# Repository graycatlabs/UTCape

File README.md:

# UTCape

A BeagleBone Black cape to support unit tests in software libraries like PyBBIO 
and Bonsescript. 

The current concept would allow testing of GPIO, UART, SPI, I2C, ADC, eCAP, PWM,
and eQEP software.

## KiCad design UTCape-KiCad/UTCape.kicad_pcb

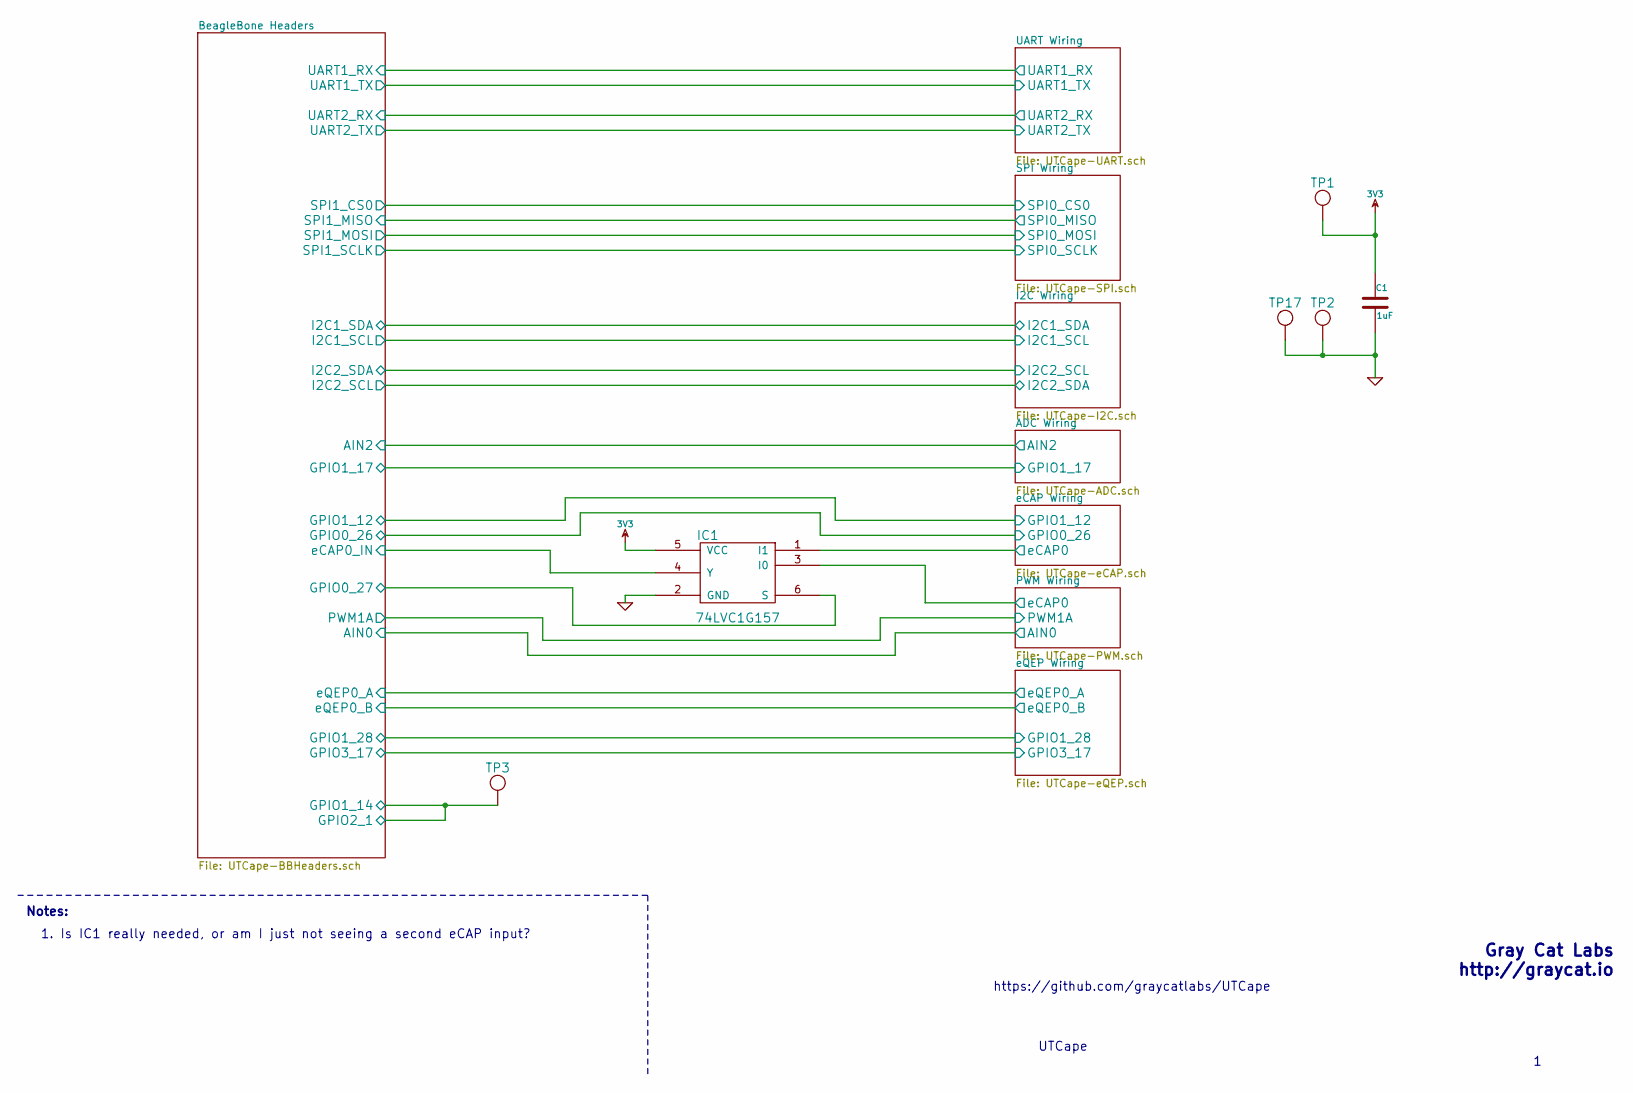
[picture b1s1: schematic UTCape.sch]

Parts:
C1: 1uF
IC1: 74LVC1G157
TP1, TP2, TP3, TP17: TEST_POINT

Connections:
3V3: C1.1, IC1.5 (VCC), TP1.1; also elsewhere on the board
/BeagleBone Headers/GPIO0_27: IC1.6 (S); also elsewhere on the board
/BeagleBone Headers/GPIO2_1: TP3.1; also elsewhere on the board
/BeagleBone Headers/PWM1A: IC1.3 (I0); also elsewhere on the board
/BeagleBone Headers/eCAP0_IN: IC1.4 (Y); also elsewhere on the board
/eCAP Wiring/eCAP0: IC1.1 (I1); also elsewhere on the board
GND: C1.2, IC1.2 (GND), TP2.1, TP17.1; also elsewhere on the board

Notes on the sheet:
UTCape
Gray Cat Labs http://graycat.io
https://github.com/graycatlabs/UTCape
Notes:
1. Is IC1 really needed, or am I just not seeing a second eCAP input?

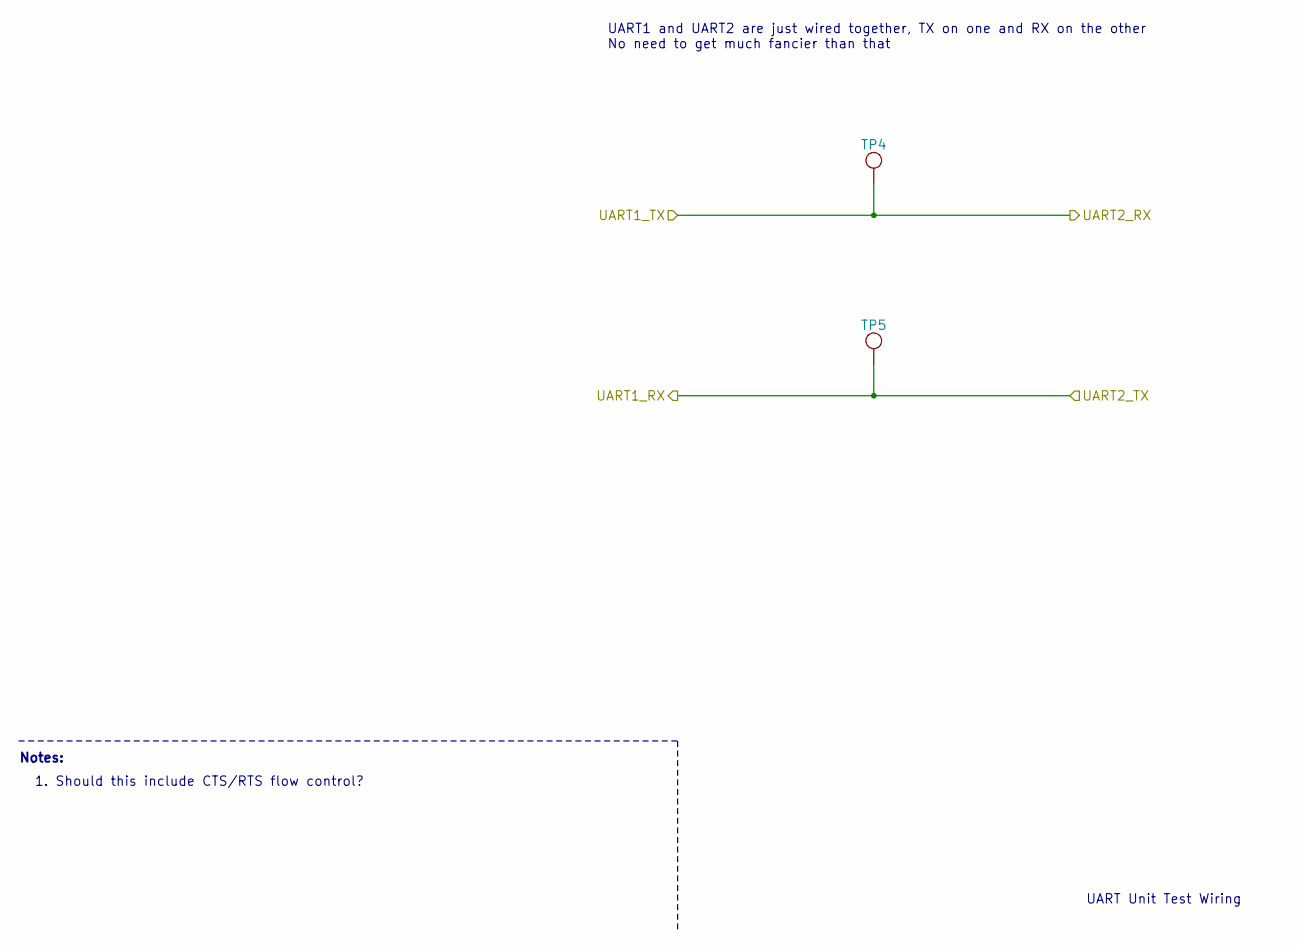
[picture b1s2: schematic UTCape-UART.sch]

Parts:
TP4, TP5: TEST_POINT

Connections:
/BeagleBone Headers/UART1_RX: TP5.1; also elsewhere on the board
/BeagleBone Headers/UART1_TX: TP4.1; also elsewhere on the board

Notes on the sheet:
UART Unit Test Wiring
UART1 and UART2 are just wired together, TX on one and RX on the other No need to get much fancier than that
1. Should this include CTS/RTS flow control?
Notes:

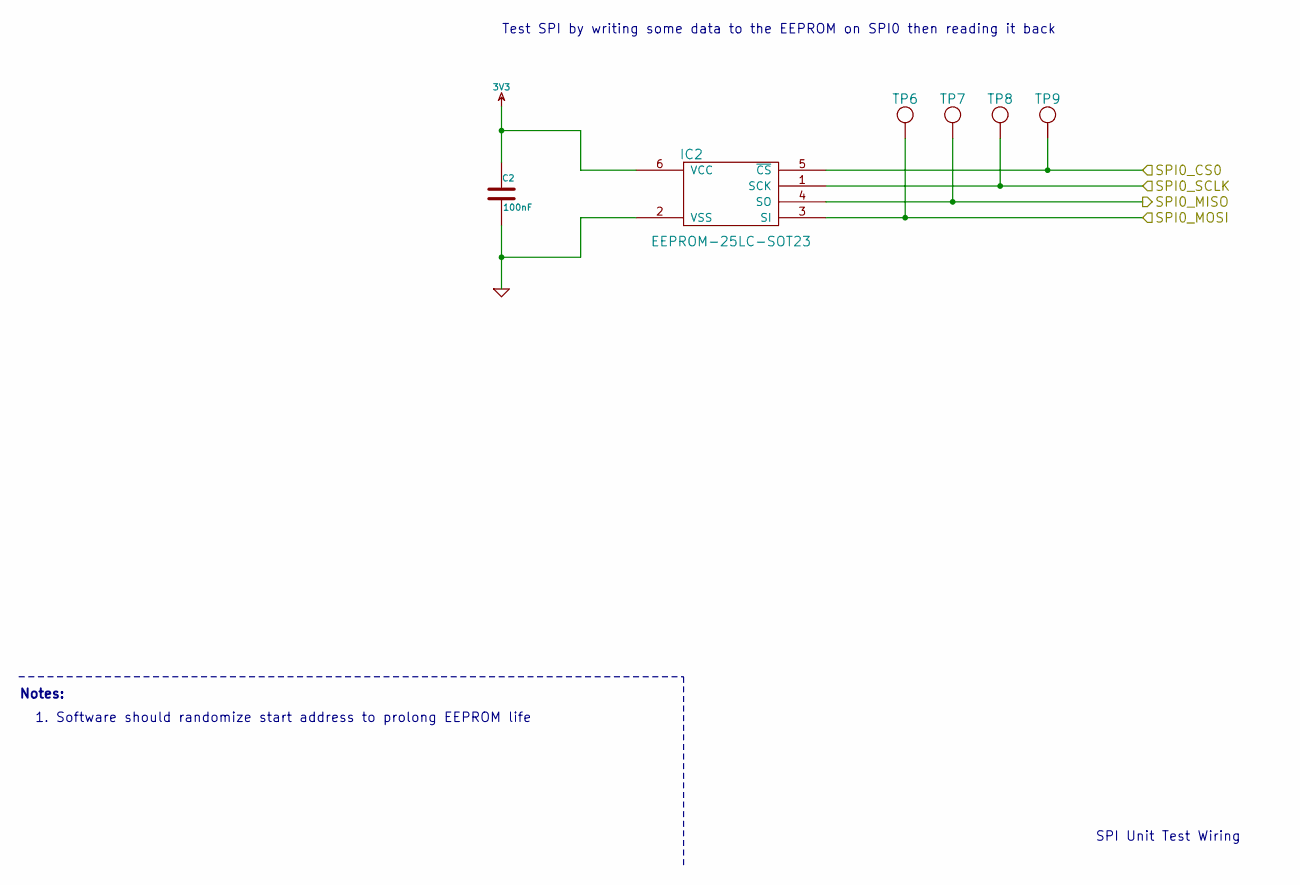
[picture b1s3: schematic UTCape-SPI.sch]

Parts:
C2: 100nF
IC2: EEPROM-25LC-SOT23
TP6, TP7, TP8, TP9: TEST_POINT

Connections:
3V3: C2.1, IC2.6 (VCC); also elsewhere on the board
/SPI Wiring/SPI0_CS0: IC2.5 (~CS), TP9.1; also elsewhere on the board
/SPI Wiring/SPI0_MISO: IC2.4 (SO), TP7.1; also elsewhere on the board
/SPI Wiring/SPI0_MOSI: IC2.3 (SI), TP6.1; also elsewhere on the board
/SPI Wiring/SPI0_SCLK: IC2.1 (SCK), TP8.1; also elsewhere on the board
GND: C2.2, IC2.2 (VSS); also elsewhere on the board

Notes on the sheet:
SPI Unit Test Wiring
Test SPI by writing some data to the EEPROM on SPI0 then reading it back
Notes:
1. Software should randomize start address to prolong EEPROM life

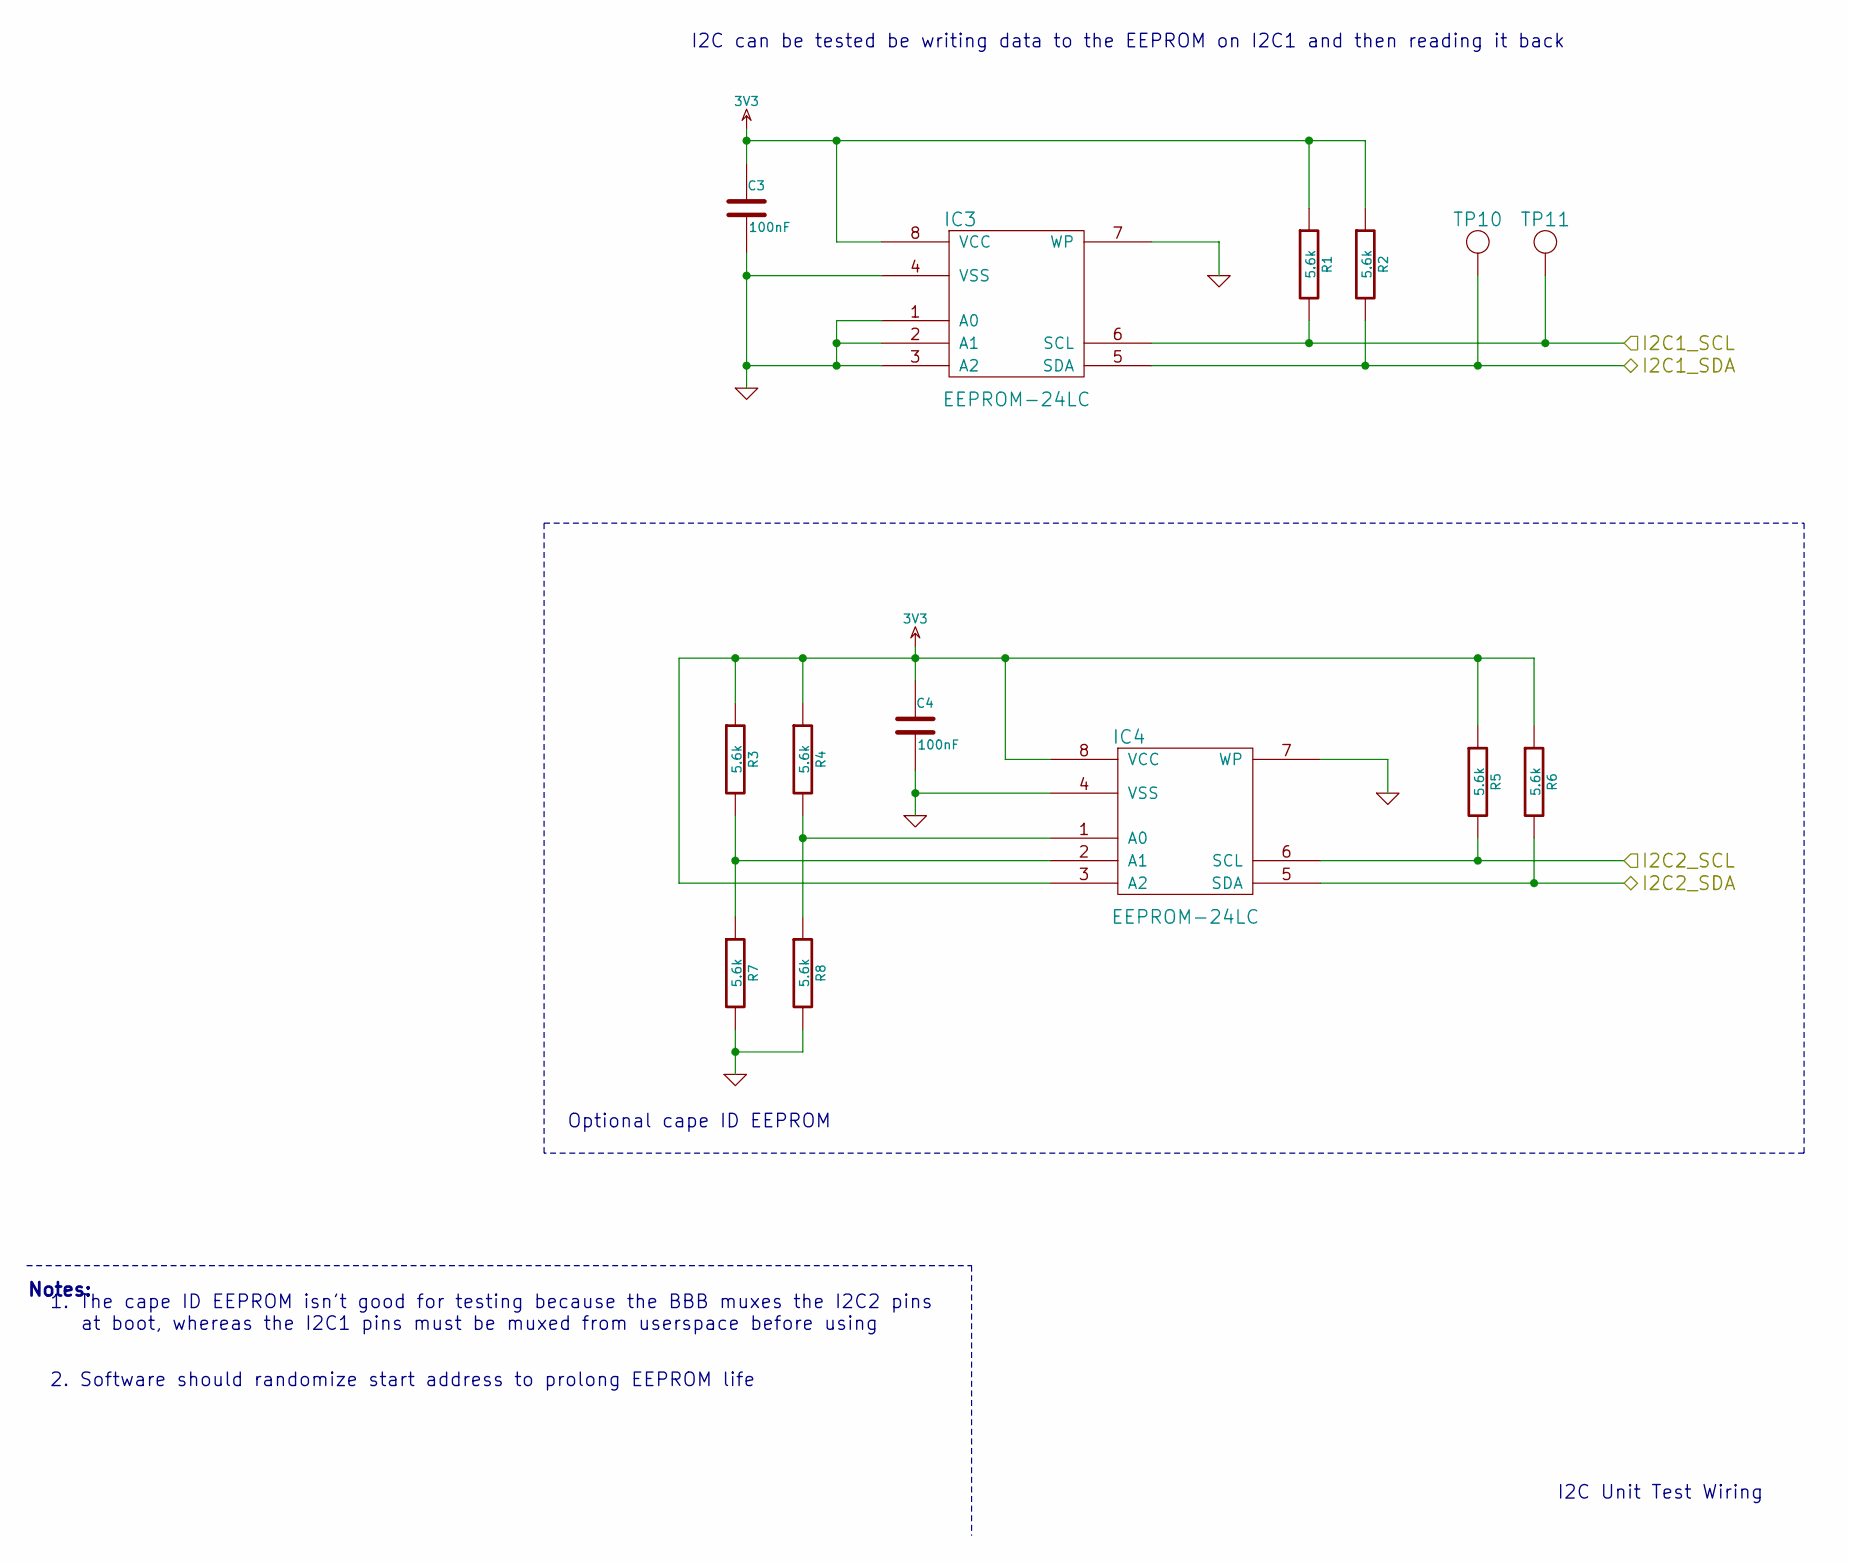
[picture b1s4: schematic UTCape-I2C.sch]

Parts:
C3, C4: 100nF
IC3, IC4: EEPROM-24LC
R1, R2, R3, R4, R5, R6, R7, R8: 5.6k
TP10, TP11: TEST_POINT

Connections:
3V3: C3.1, C4.1, IC3.8 (VCC), IC4.3 (A2), IC4.8 (VCC), R1.1, R2.1, R3.1, R4.1, R5.1, R6.1; also elsewhere on the board
/BeagleBone Headers/I2C1_SCL: IC3.6 (SCL), R1.2, TP11.1; also elsewhere on the board
/BeagleBone Headers/I2C1_SDA: IC3.5 (SDA), R2.2, TP10.1; also elsewhere on the board
/BeagleBone Headers/I2C2_SCL: IC4.5 (SDA), R6.2; also elsewhere on the board
/I2C Wiring/I2C2_SCL: IC4.6 (SCL), R5.2; also elsewhere on the board
GND: C3.2, C4.2, IC3.1 (A0), IC3.2 (A1), IC3.3 (A2), IC3.4 (VSS), IC3.7 (WP), IC4.4 (VSS), IC4.7 (WP), R7.2, R8.2; also elsewhere on the board
unnamed: IC4.1 (A0), R4.2, R8.1
unnamed: IC4.2 (A1), R3.2, R7.1

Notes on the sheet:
I2C Unit Test Wiring
Optional cape ID EEPROM
I2C can be tested be writing data to the EEPROM on I2C1 and then reading it back
Notes:
1. The cape ID EEPROM isn't good for testing because the BBB muxes the I2C2 pins at boot, whereas the I2C1 pins must be muxed from userspace before using
2. Software should randomize start address to prolong EEPROM life

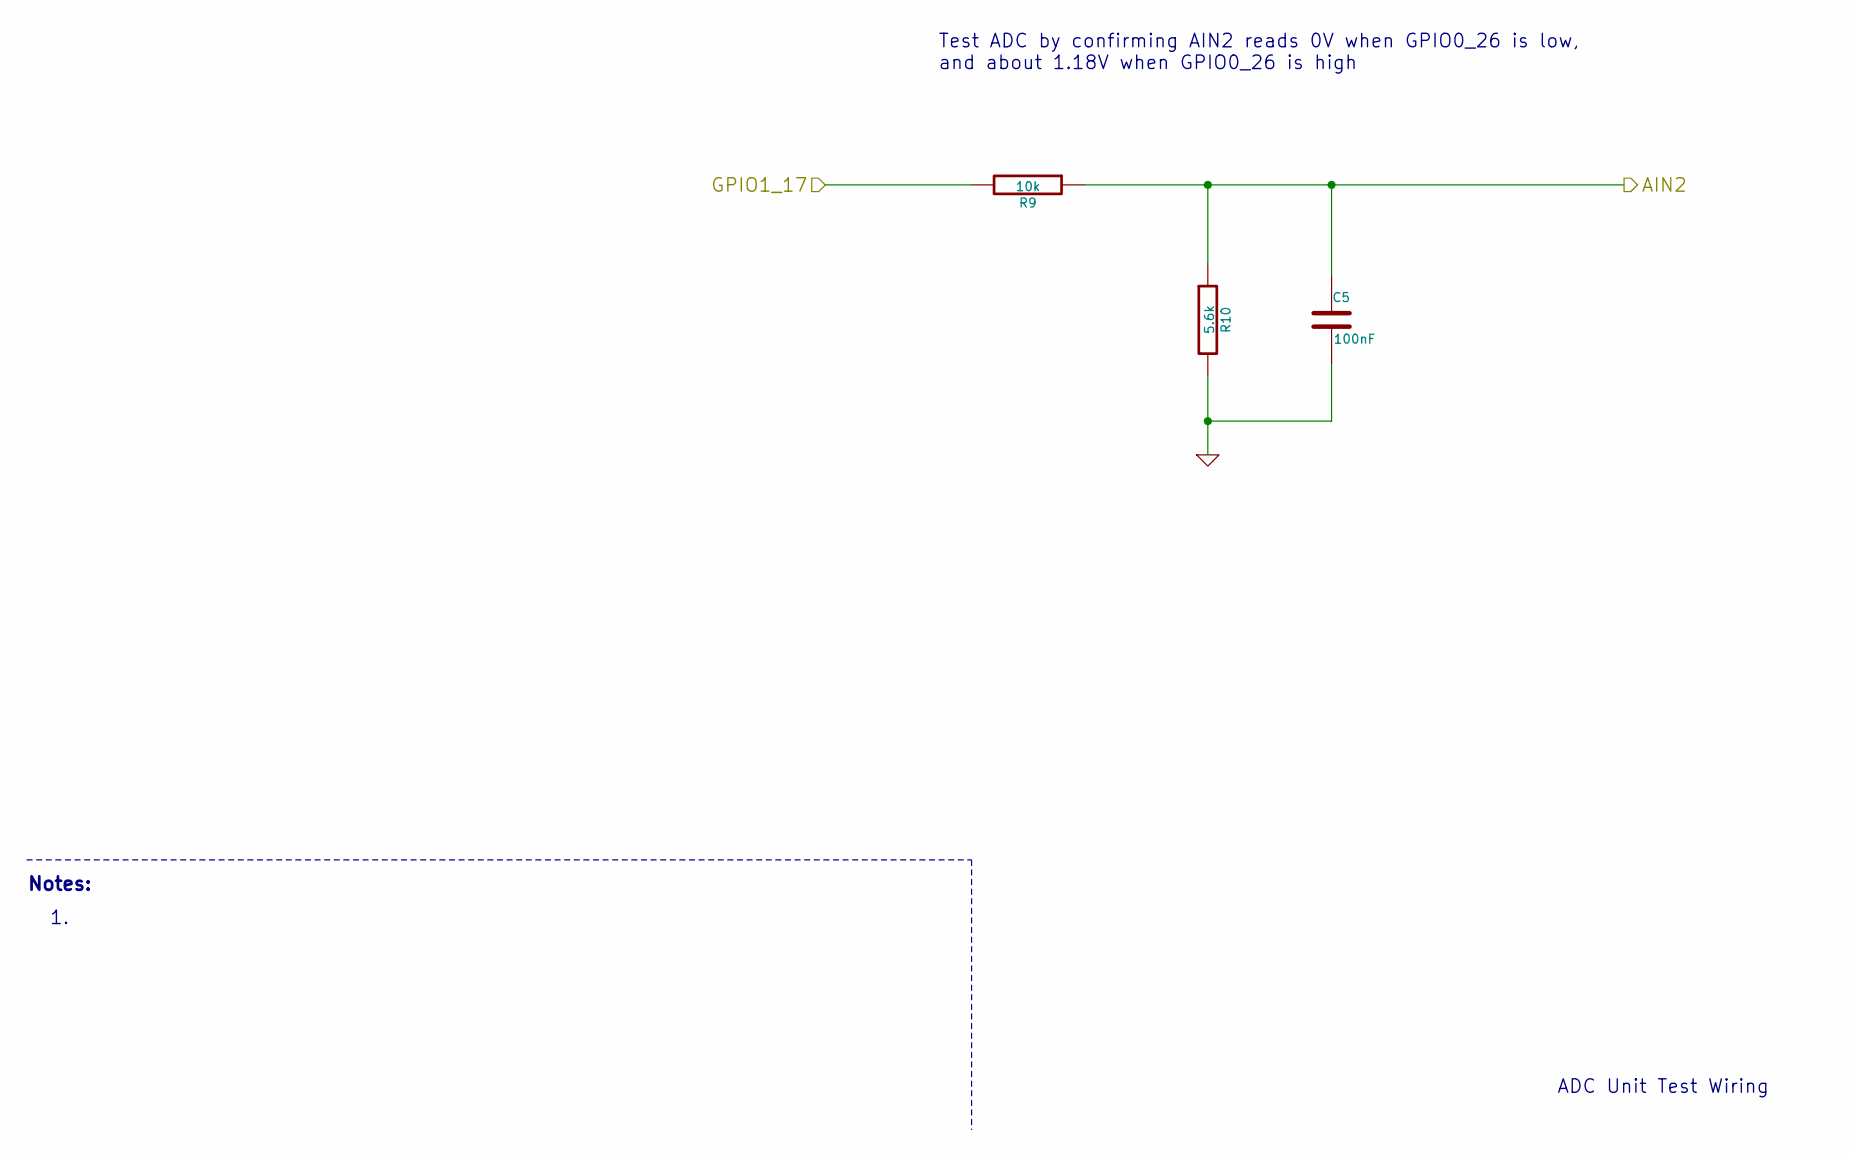
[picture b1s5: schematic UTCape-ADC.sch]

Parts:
C5: 100nF
R9: 10k
R10: 5.6k

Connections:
/ADC Wiring/AIN2: C5.1, R9.1, R10.1; also elsewhere on the board
/ADC Wiring/GPIO1_17: R9.2; also elsewhere on the board
GND: C5.2, R10.2; also elsewhere on the board

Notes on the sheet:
ADC Unit Test Wiring
Notes:
Test ADC by confirming AIN2 reads 0V when GPIO0_26 is low, and about 1.18V when GPIO0_26 is high

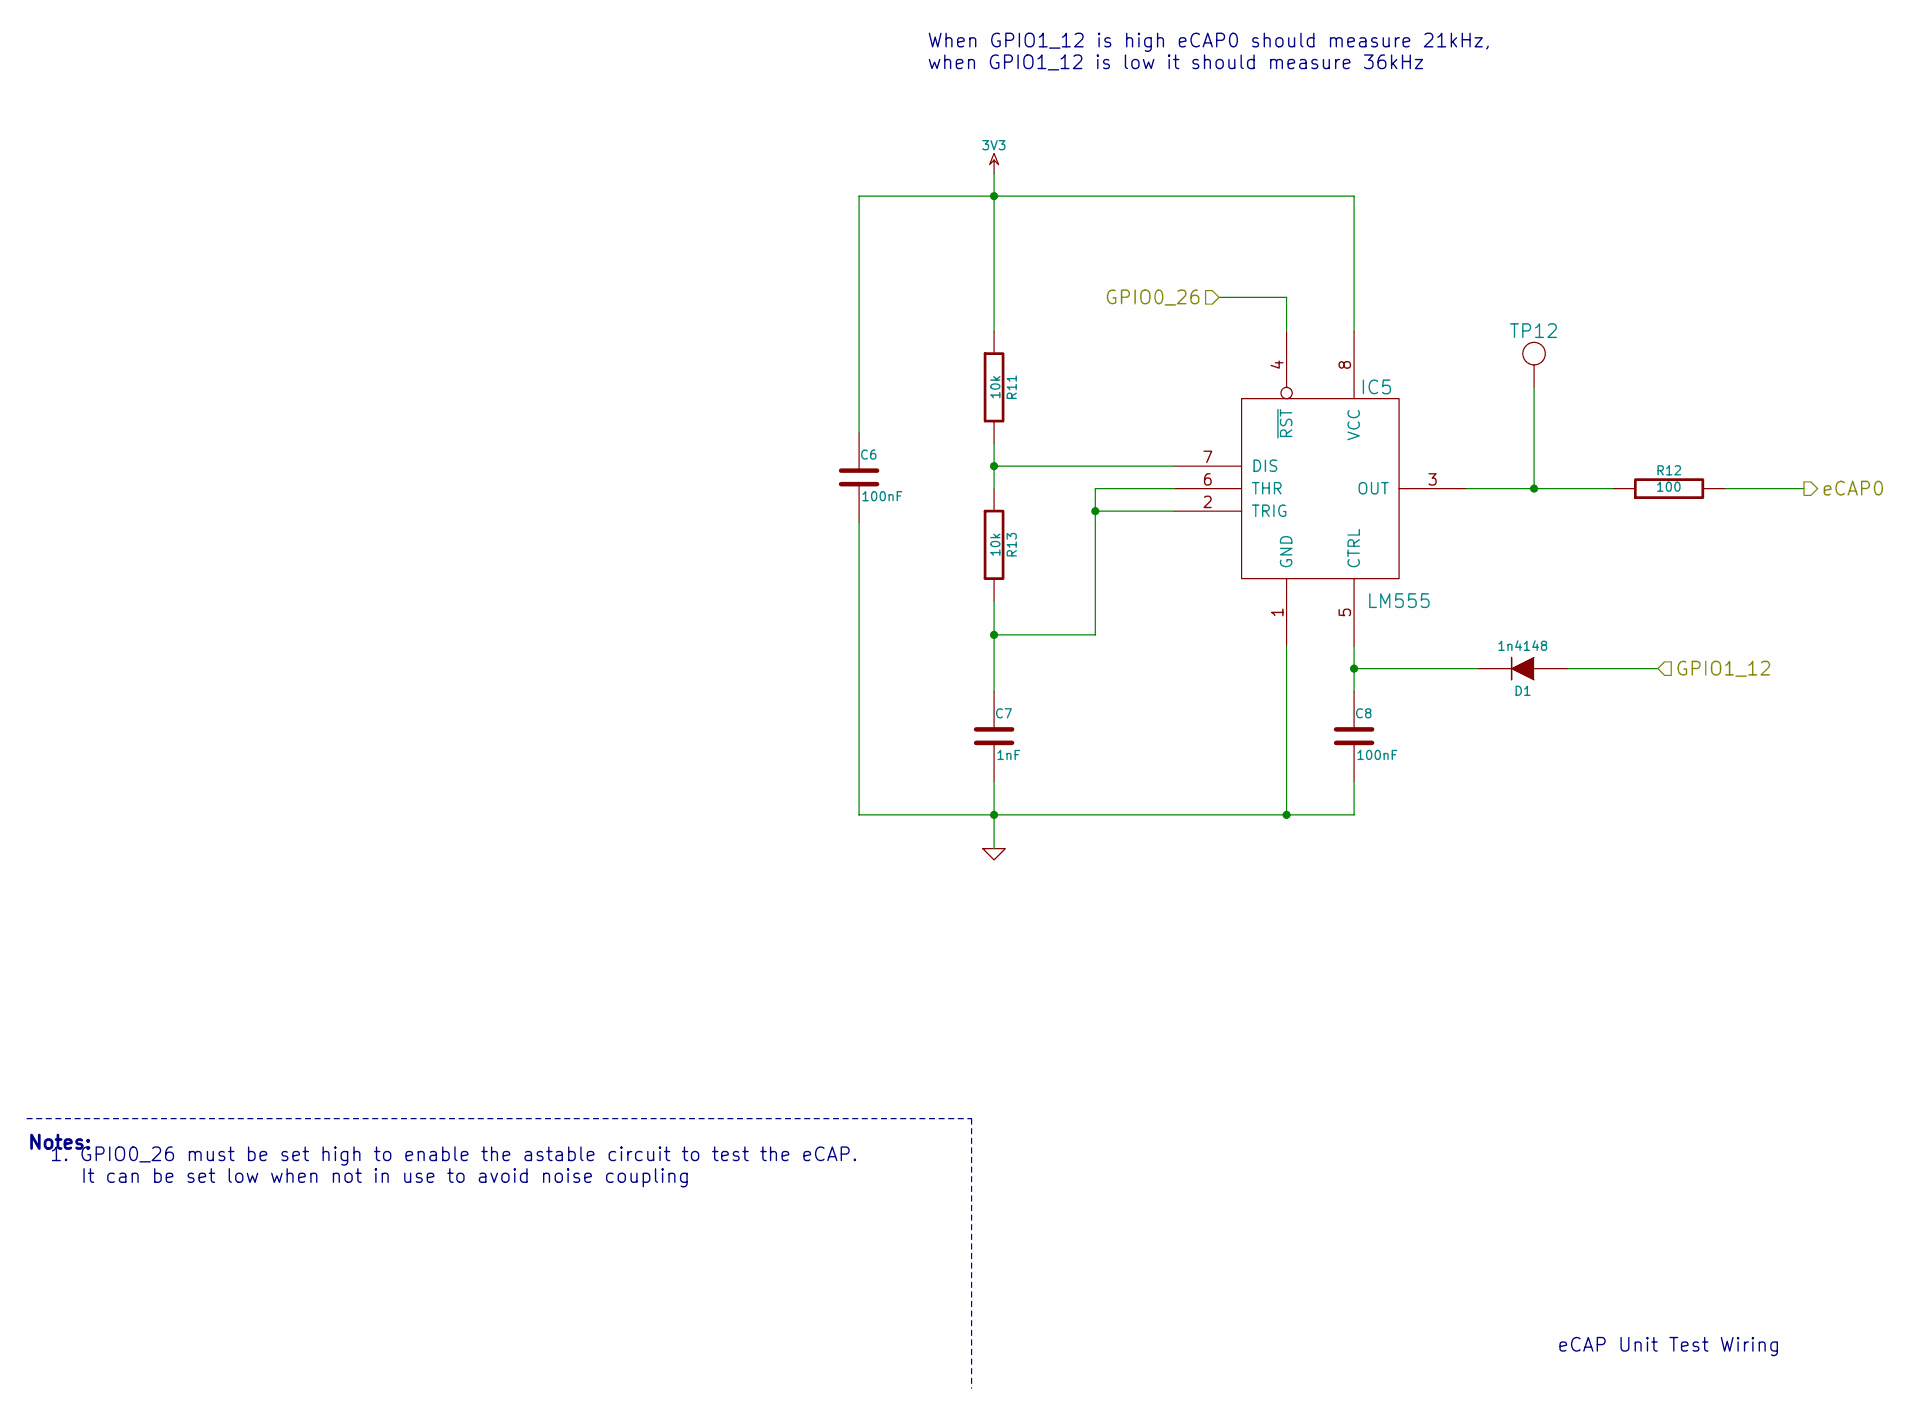
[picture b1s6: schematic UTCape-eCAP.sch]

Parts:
C6, C8: 100nF
C7: 1nF
D1: 1n4148
IC5: LM555
R11, R13: 10k
R12: 100
TP12: TEST_POINT

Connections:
3V3: C6.1, IC5.8 (VCC), R11.1; also elsewhere on the board
/BeagleBone Headers/GPIO0_26: IC5.4 (~RST); also elsewhere on the board
/BeagleBone Headers/GPIO1_12: D1.1 (A); also elsewhere on the board
/eCAP Wiring/eCAP0: R12.2; also elsewhere on the board
GND: C6.2, C7.2, C8.2, IC5.1 (GND); also elsewhere on the board
unnamed: IC5.7 (DIS), R11.2, R13.1
unnamed: IC5.3 (OUT), R12.1, TP12.1
unnamed: C8.1, D1.2 (K), IC5.5 (CTRL)
unnamed: C7.1, IC5.2 (TRIG), IC5.6 (THR), R13.2

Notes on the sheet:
Notes:
1. GPIO0_26 must be set high to enable the astable circuit to test the eCAP. It can be set low when not in use to avoid noise coupling
When GPIO1_12 is high eCAP0 should measure 21kHz, when GPIO1_12 is low it should measure 36kHz
eCAP Unit Test Wiring

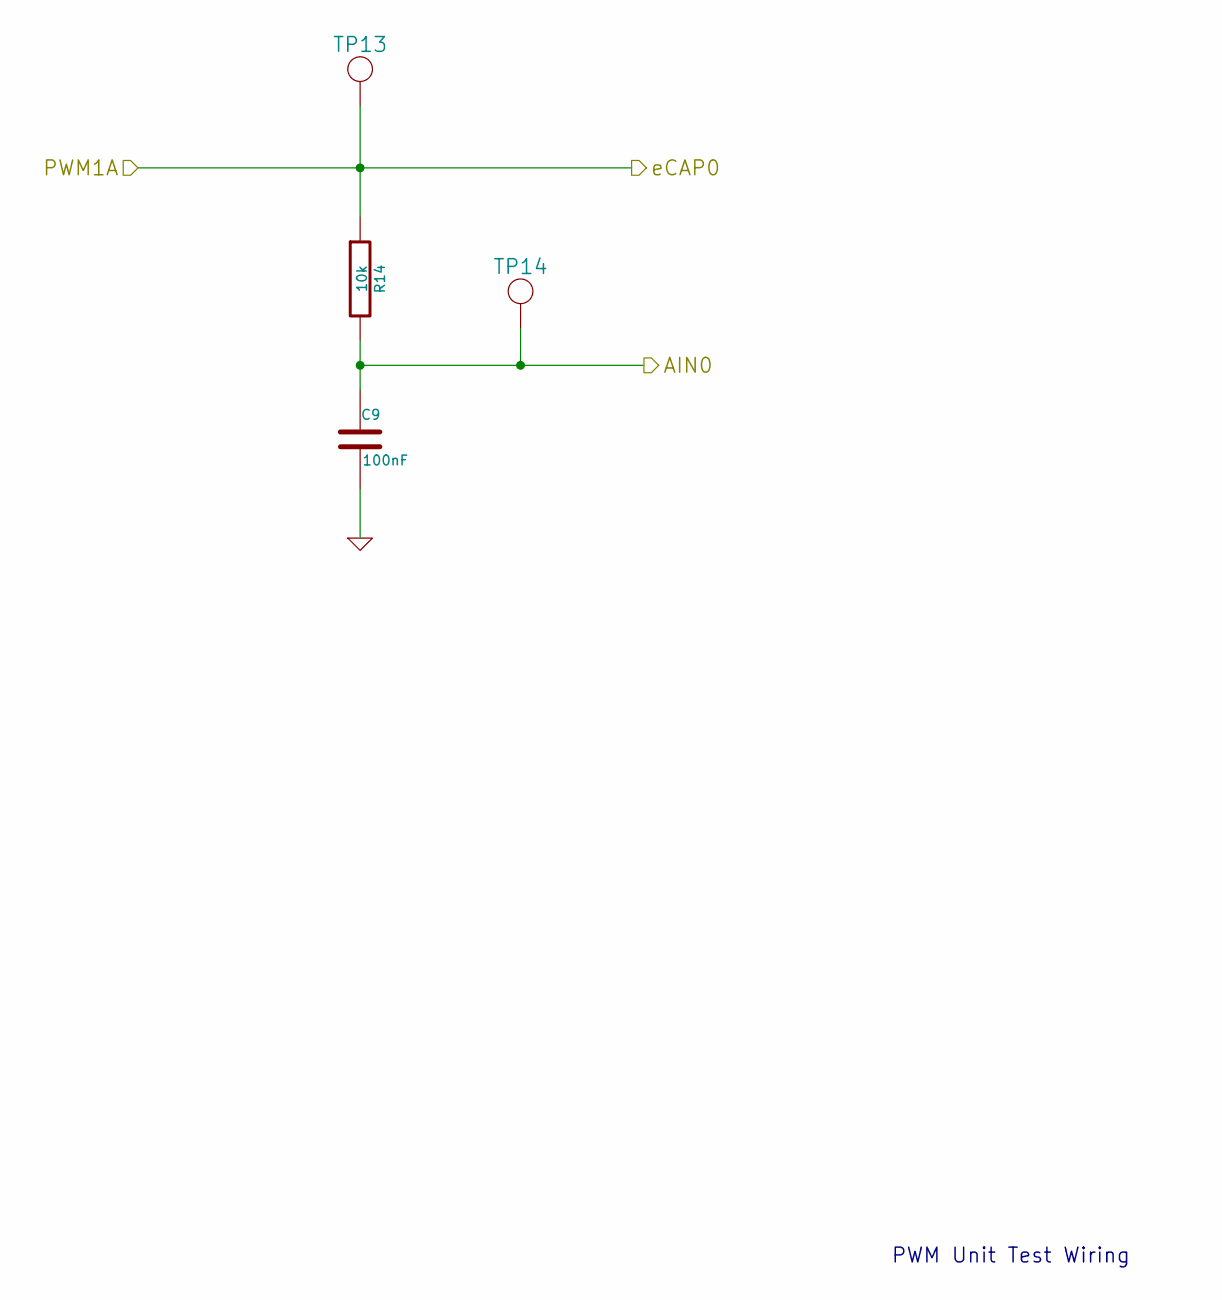
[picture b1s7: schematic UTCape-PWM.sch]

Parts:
C9: 100nF
R14: 10k
TP13, TP14: TEST_POINT

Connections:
/BeagleBone Headers/AIN0: C9.1, R14.2, TP14.1; also elsewhere on the board
/BeagleBone Headers/PWM1A: R14.1, TP13.1; also elsewhere on the board
GND: C9.2; also elsewhere on the board

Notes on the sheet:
PWM Unit Test Wiring

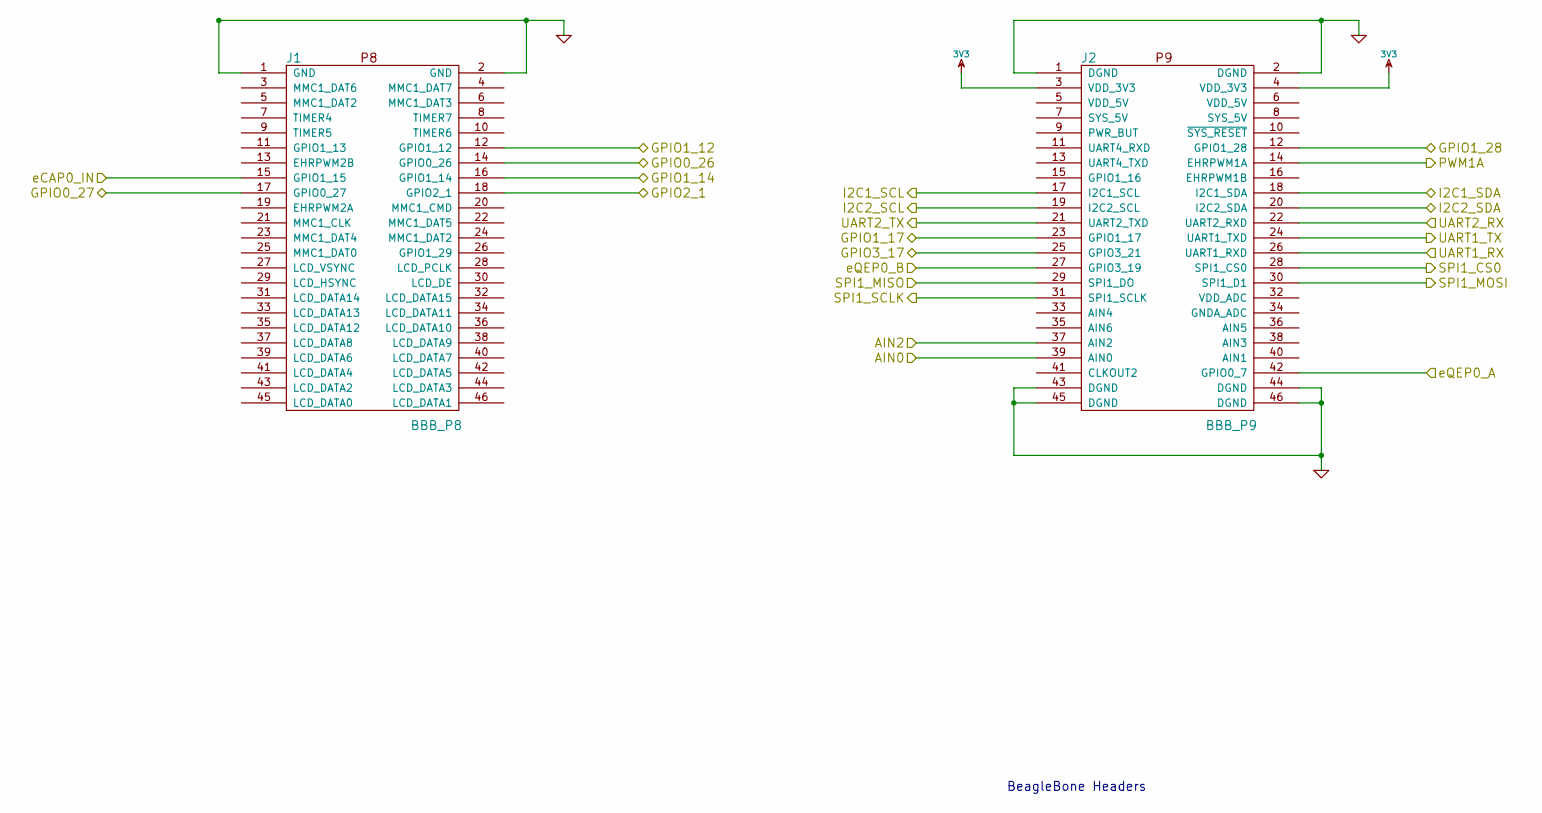
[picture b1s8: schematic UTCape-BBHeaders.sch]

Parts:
J1: BBB_P8
J2: BBB_P9

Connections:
3V3: J2.3 (VDD_3V3), J2.4 (VDD_3V3); also elsewhere on the board
/ADC Wiring/AIN2: J2.37 (AIN2); also elsewhere on the board
/ADC Wiring/GPIO1_17: J2.23 (GPIO1_17); also elsewhere on the board
/BeagleBone Headers/AIN0: J2.39 (AIN0); also elsewhere on the board
/BeagleBone Headers/GPIO0_20: J2.41 (CLKOUT2); also elsewhere on the board
/BeagleBone Headers/GPIO0_26: J1.14 (GPIO0_26); also elsewhere on the board
/BeagleBone Headers/GPIO0_27: J1.17 (GPIO0_27); also elsewhere on the board
/BeagleBone Headers/GPIO1_12: J1.12 (GPIO1_12); also elsewhere on the board
/BeagleBone Headers/GPIO1_14: J1.16 (GPIO1_14); also elsewhere on the board
/BeagleBone Headers/GPIO2_1: J1.18 (GPIO2_1); also elsewhere on the board
/BeagleBone Headers/GPIO3_17: J2.25 (GPIO3_21); also elsewhere on the board
/BeagleBone Headers/I2C1_SCL: J2.17 (I2C1_SCL); also elsewhere on the board
/BeagleBone Headers/I2C1_SDA: J2.18 (I2C1_SDA); also elsewhere on the board
/BeagleBone Headers/I2C2_SCL: J2.19 (I2C2_SCL); also elsewhere on the board
/BeagleBone Headers/PWM1A: J2.14 (EHRPWM1A); also elsewhere on the board
/BeagleBone Headers/UART1_RX: J2.26 (UART1_RXD); also elsewhere on the board
/BeagleBone Headers/UART1_TX: J2.24 (UART1_TXD); also elsewhere on the board
/BeagleBone Headers/UART2_RX: J2.22 (UART2_RXD); also elsewhere on the board
/BeagleBone Headers/UART2_TX: J2.21 (UART2_TXD); also elsewhere on the board
/BeagleBone Headers/eCAP0_IN: J1.15 (GPIO1_15); also elsewhere on the board
/BeagleBone Headers/eQEP0_A: J2.42 (GPIO0_7); also elsewhere on the board
/BeagleBone Headers/eQEP0_B: J2.27 (GPIO3_19); also elsewhere on the board
/I2C Wiring/I2C2_SCL: J2.20 (I2C2_SDA); also elsewhere on the board
/SPI Wiring/SPI0_CS0: J2.28 (SPI1_CS0); also elsewhere on the board
/SPI Wiring/SPI0_MISO: J2.29 (SPI1_DO); also elsewhere on the board
/SPI Wiring/SPI0_MOSI: J2.30 (SPI1_D1); also elsewhere on the board
/SPI Wiring/SPI0_SCLK: J2.31 (SPI1_SCLK); also elsewhere on the board
GND: J1.1 (GND), J1.2 (GND), J2.1 (DGND), J2.2 (DGND), J2.43 (DGND), J2.44 (DGND), J2.45 (DGND), J2.46 (DGND); also elsewhere on the board

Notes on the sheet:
BeagleBone Headers

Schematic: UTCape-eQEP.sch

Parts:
TP15, TP16: TEST_POINT

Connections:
/BeagleBone Headers/GPIO0_20: TP15.1; also elsewhere on the board
/BeagleBone Headers/GPIO3_17: TP16.1; also elsewhere on the board

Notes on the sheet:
eQEP Unit Test Wiring

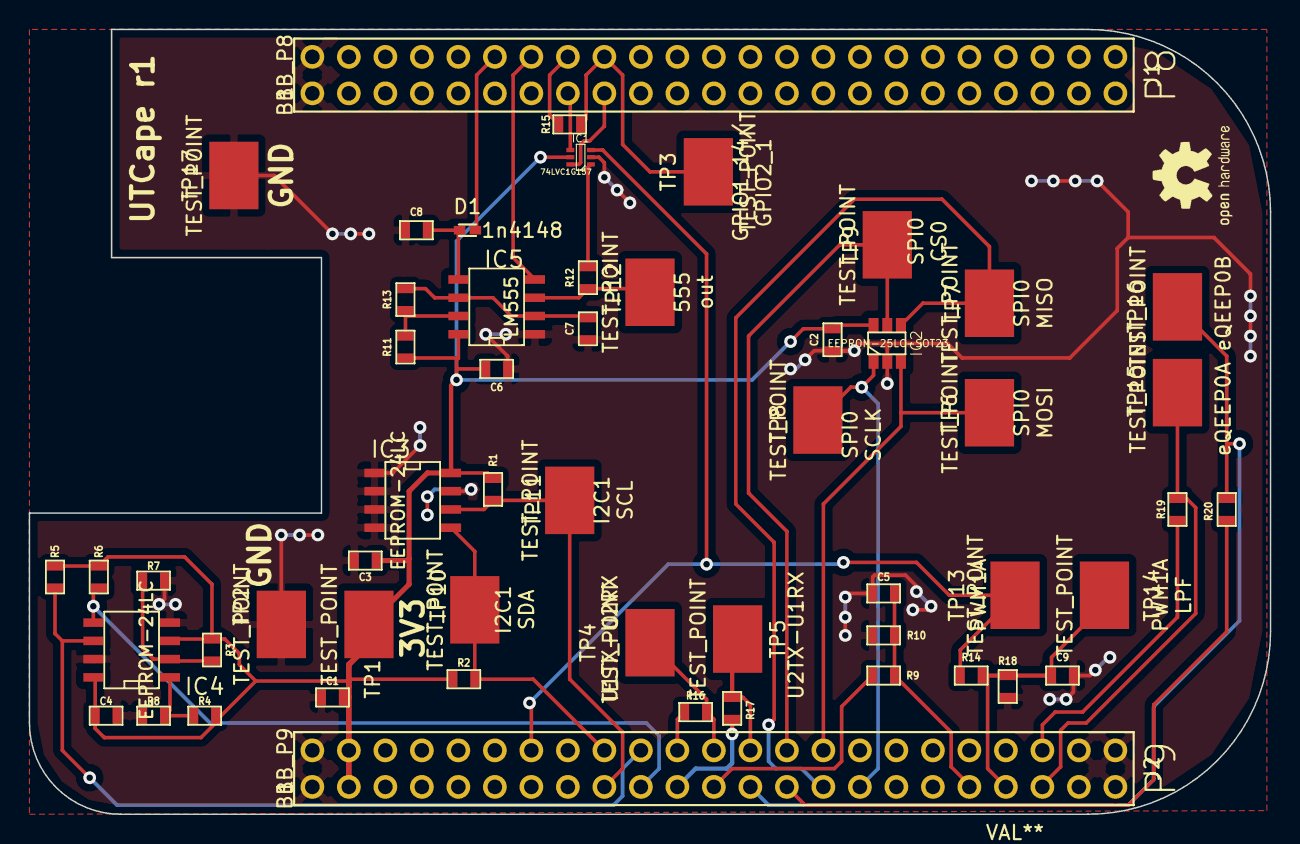
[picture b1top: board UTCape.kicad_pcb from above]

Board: 2 copper layers, 86.4 x 54.6 mm, 55 parts (0 on the bottom side), 35 nets.

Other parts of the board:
BBBCapeGuide: VAL**; BBBCapeGuide
R15, R16, R17, R19, R20: 100; SM0603
R18: 5.6k; SM0603

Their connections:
/BeagleBone Headers/AIN0: R18.1; also elsewhere on the board
/BeagleBone Headers/GPIO0_20: R19.1; also elsewhere on the board
/BeagleBone Headers/GPIO1_14: R15.1; also elsewhere on the board
/BeagleBone Headers/GPIO2_1: R15.2; also elsewhere on the board
/BeagleBone Headers/GPIO3_17: R20.1; also elsewhere on the board
/BeagleBone Headers/UART1_RX: R17.1; also elsewhere on the board
/BeagleBone Headers/UART1_TX: R16.1; also elsewhere on the board
/BeagleBone Headers/UART2_RX: R16.2; also elsewhere on the board
/BeagleBone Headers/UART2_TX: R17.2; also elsewhere on the board
/BeagleBone Headers/eQEP0_A: R19.2; also elsewhere on the board
/BeagleBone Headers/eQEP0_B: R20.2; also elsewhere on the board
GND: R18.2; also elsewhere on the board

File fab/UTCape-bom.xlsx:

# | Designator | Quantity | Description | Manufacturer | Mfg. part number | Supplier | Supplier part number | URL
1 | C1 | 1 | CAP CER 10000PF 50V 10% X7R 0603 | Murata | GRM188R71H103KA01D | Digi-Key | 490-1512-1-ND | http://www.digikey.com/product-detail/en/GRM188R71H103KA01D/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
2 | C2 C3 C4 C5 C6 C8 C9 | 7 | CAP CER 0.1UF 50V 10% X7R 0603 | Murata | GRM188R71H104KA93D | Digi-Key | 490-1519-1-ND | http://www.digikey.com/product-detail/en/GRM188R71H104KA93D/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
3 | C7 | 1 | CAP CER 1000PF 50V 10% X7R 0603 | Murata | GRM188R71H102KA01D | Digi-Key | 490-1494-1-ND | http://www.digikey.com/product-detail/en/GRM188R71H102KA01D/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
4 | D1 | 1 | DIODE GEN PURP 75V 150MA SOD523 | Micro Commercial Co | 1N4148X-TP | Digi-Key | 1N4148XTPMSCT-ND | http://www.digikey.com/product-detail/en/1N4148X-TP/1N4148XT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
5 | IC1 | 1 | IC SINGLE 2-INPUT MUX 6TSSOP | NXP Semiconductors | 74LVC1G157GW,125 | Digi-Key | 568-3008-1-ND | http://www.digikey.com/product-detail/en/74LVC1G157GW,125/568-3008-1-ND/1023416
6 | IC2 | 1 | IC EEPROM 1KBIT 10MHZ SOT23-6 | Microchip | 25LC010AT-I/OT | Digi-Key | 25LC010AT-I/OTCT-ND | http://www.digikey.com/product-detail/en/25LC010AT-I%2FOT/25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
7 | IC3 IC4 | 2 | IC EEPROM 256KBIT 400KHZ 8SOIC | Microchip | 24LC256T-I/SN | Digi-Key | 24LC256T-I/SNCT-ND | http://www.digikey.com/product-detail/en/24LC01BT-I%2FOT/24L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
8 | IC5 | 1 | IC OSC SGL TIMER 2.1MHZ 8-SOIC | Texas Instruments | TLC555CDR | Digi-Key | 296-1336-1-ND | http://www.digikey.com/product-detail/en/TLC555CDR/296-1336-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
9 | J1, J2 | 1 | CONN HEADER .100" DUAL STR 46POS | Sullins Connector Solutions | PREC023DAAN-RC | Digi-Key | S2012EC-23-ND | http://www.digikey.com/product-detail/en/PREC023DAAN-RC/S201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
10 | R1 R2 R3 R4 R5 R6 R7 R8 R10 R18 | 10 | RES SMD 5.6K OHM 1% 1/10W 0603 | Rohm Semiconductor | MCR03ERTF5601 | Digi-Key | RHM5.6KCFCT-ND | http://www.digikey.com/product-detail/en/MCR03ERTF5601/RHM5.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
11 | R9 R11 R13 R14 | 4 | RES SMD 10K OHM 1% 1/10W 0603 | Rohm Semiconductor | MCR03EZPFX1002 | Digi-Key | RHM10.0KHCT-ND | http://www.digikey.com/product-detail/en/MCR03EZPFX1002/RHM1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
12 | R12 R15 R16 R17 R19 R20 | 6 | RES SMD 100 OHM 1% 1/10W 0603 | Rohm Semiconductor | MCR03ERTF1000 | Digi-Key | RHM100CFCT-ND | http://www.digikey.com/product-detail/en/MCR03ERTF1000/RHM10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
13 | TP1 TP2 TP3 TP4 TP5 TP6 TP7 TP8 TP9 TP10 TP11 TP12 TP13 TP14 TP15 TP16 TP17 | 17 | PC TEST POINT COMPACT SMT | Keystone Electronics | 5016 | Digi-Key | 5016KCT-ND | http://www.digikey.com/product-detail/en/5016/5016KCT-ND/278888

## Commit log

2015-02-24 first commit of the UTCape
2015-02-24 added missing title, created pdf of schematics
2015-02-24 cleaned up directories, added libraries
2015-02-24 layed out PCB, some minor wiring changes for layout
2015-02-24 generated gerber and drill files
2015-03-24 added missing resistor in divider plus some protection resistors, regenerated fab files
2015-03-24 added BOM
2015-03-24 moved some reference designators
2015-03-25 regenerated schematic
